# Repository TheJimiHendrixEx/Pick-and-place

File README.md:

# Pick-and-place
This repository will hold all of the code required for the user interface on a computer as well as the code that will be run on a arduino.

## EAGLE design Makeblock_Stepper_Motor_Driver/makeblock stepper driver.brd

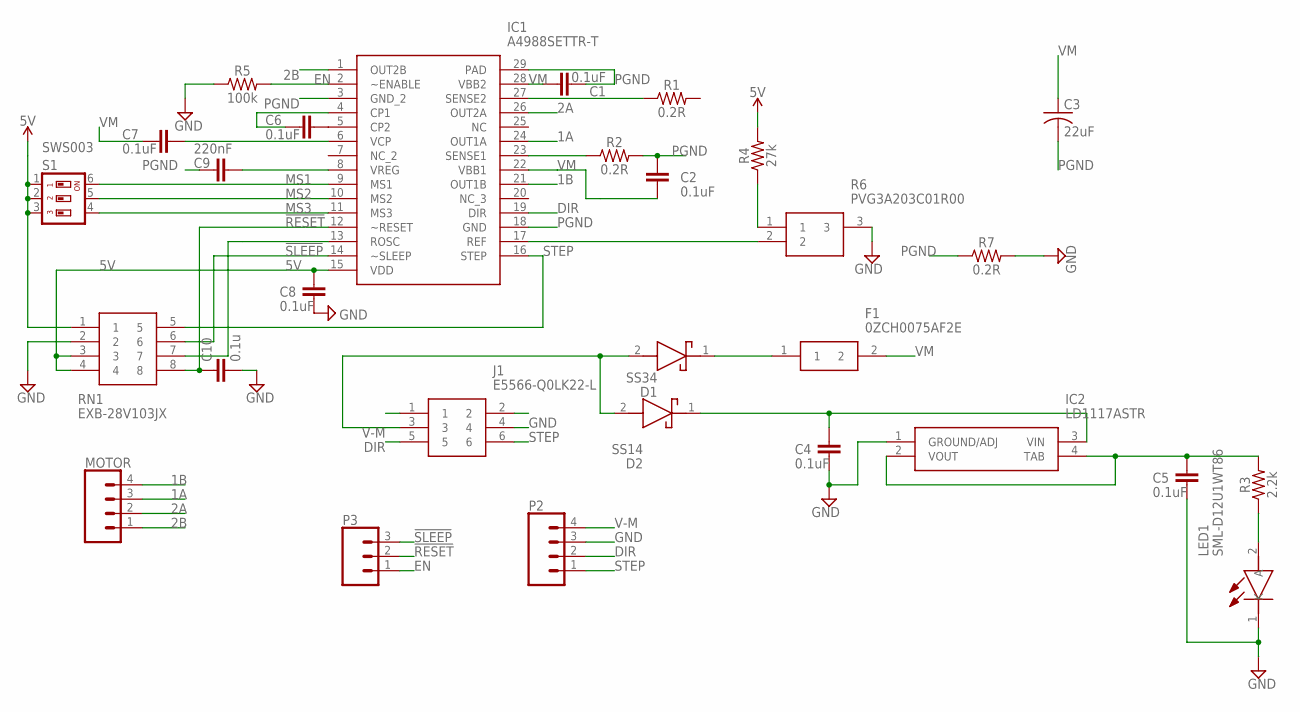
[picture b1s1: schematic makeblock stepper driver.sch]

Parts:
C1, C2, C4, C5, C6, C7, C8: 0.1uF; C0402
C3: 22uF; C025-024X044
C9: 220nF; C0402
C10: 0.1u; C0402
D1: SS34; DIOM8059X256N
D2: SS14; DIOM5227X270N
F1: 0ZCH0075AF2E; FUSC3226X75N
IC1: A4988SETTR-T; QFN50P500X500X100-29N
IC2: LD1117ASTR; SOT230P700X180-4N
J1: E5566-Q0LK22-L; E5566Q0LK22L
LED1: SML-D12U1WT86; LEDC1608X65N
MOTOR: CONN_04JST-PTH-VERT; JST-4-PTH-VERT
P2: CONN_04PTH; 1X04
P3: CONN_03LOCK; 1X03_LOCK
R1, R2, R7: 0.2R; 0603
R3: 2.2k; 0603
R4: 27k; 0603
R5: 100k; 0603
R6: PVG3A203C01R00
RN1: EXB-28V103JX; EXB28V_1
S1: SWS003; SMS-003

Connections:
1A: IC1.24 (OUT1A), MOTOR.3
1B: IC1.21 (OUT1B), MOTOR.4
2A: IC1.26 (OUT2A), MOTOR.2
2B: IC1.1 (OUT2B), MOTOR.1
5V: C8.2, IC1.15 (VDD), R4.2, RN1.1, RN1.3, RN1.4, S1.1, S1.2, S1.3
!RESET: C10.1, IC1.12 (~RESET), P3.2, RN1.8
!SLEEP: IC1.14 (~SLEEP), P3.3, RN1.6
DIR: IC1.19 (DIR), J1.5, P2.2
EN: IC1.2 (~ENABLE), P3.1, R5.2
GND: C4.1, C5.1, C8.1, C10.2, IC2.1 (GROUND/ADJ), J1.4, LED1.1 (K), P2.3, R5.1, R6.3, R7.2, RN1.2
MS1: IC1.9 (MS1), S1.6
MS2: IC1.10 (MS2), S1.5
MS3: IC1.11 (MS3), S1.4
unnamed: C6.2, IC1.5 (CP2)
unnamed: C6.1, IC1.4 (CP1)
unnamed: D1.1 (K), F1.1
unnamed: C4.2, D2.1 (K), IC2.3 (VIN)
unnamed: C9.2, IC1.8 (VREG)
unnamed: IC1.13 (ROSC), RN1.7
unnamed: LED1.2 (A), R3.1
unnamed: C5.2, IC2.2 (VOUT), IC2.4 (TAB), R3.2
unnamed: C7.2, IC1.6 (VCP)
unnamed: IC1.27 (SENSE2), R1.1
unnamed: IC1.23 (SENSE1), R2.1
unnamed: R4.1, R6.1
unnamed: IC1.17 (REF), R6.2
PGND: C1.1, C2.1, C3.2, C9.1, IC1.3 (GND_2), IC1.18 (GND), IC1.29 (PAD), R2.2, R7.1
STEP: IC1.16 (STEP), J1.6, P2.1, RN1.5
V-M: D1.2 (A), D2.2 (A), J1.3, P2.4
VM: C1.2, C2.2, C3.1, C7.1, F1.2, IC1.22 (VBB1), IC1.28 (VBB2)

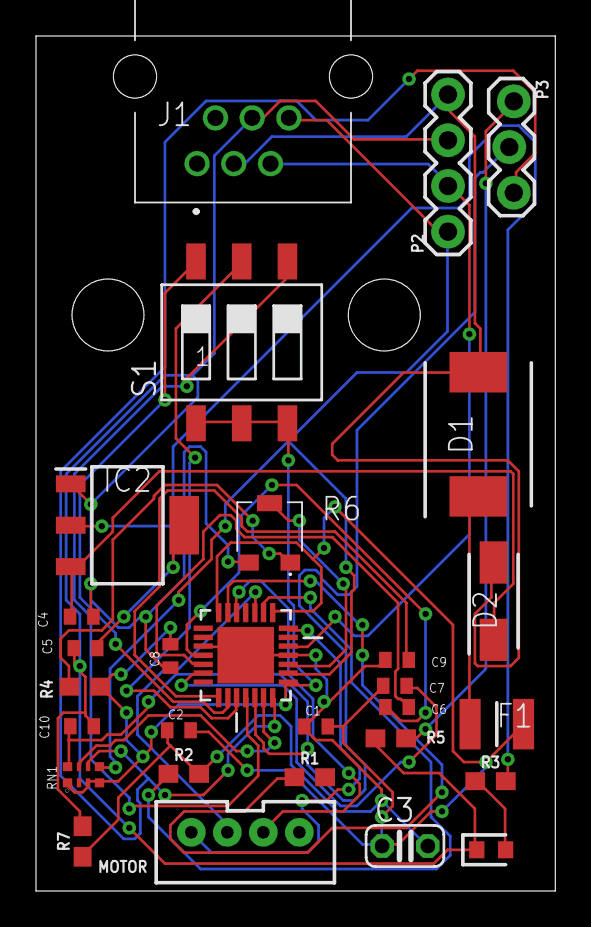
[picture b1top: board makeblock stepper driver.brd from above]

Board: 2 copper layers, 28.9 x 47.5 mm, 29 parts (0 on the bottom side), 30 nets.

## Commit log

2019-02-02 This is the first commit
2019-02-02 Deleted the temp files
2019-02-02 test commit
2019-02-02 homework
2019-02-02 deleting temp code
2019-02-05 test
2019-02-11 Created a visual studio project
2019-02-11 This is actually the project
2019-02-11 Testing visual studio
2019-02-17 Added code for the video camera
2019-02-17 All the gcode parser
2019-03-03 Installed the correct gcode parser
2019-03-08 Added keyPress event listeners, more buttons, and started to organize the controls
2019-04-06 Fixed the z axis on arduino code, added functionality to the x y and z buttons.
2019-04-07 borders and layout changes
2019-04-08 Reorganizing the UI, Resized Video Feed
2019-04-08 Added Colors
2019-04-08 dark blue border around the video feed
2019-04-09 added zero angle buton, offset functions, and offset return
2019-04-09 GUI: Added new Gcodes for zeroing
2019-04-09 added Gcode93-95
2019-04-10 added XYZA textboxes for displaying current coords
2019-04-10 added connection status box
2019-04-22 makeblock stepper motor schematic started
2019-04-22 I added a dependancy property that wull update a text box :wq
2019-04-23 Added parts to the schematic
2019-04-28 Finshed the schematic and the layout
2019-05-03 Added functionality to the zero buttons, included the lcd code in arduino,
2019-05-05 Z Stepper Limiter, A Stepper Motor functionality, New LCD custom message
2019-05-06 Added solenoid stuff
2019-05-06 button for solenoid
2019-05-06 Fixed "Go Home", Fixed Offset, Added Feedrate Control
2019-05-07 added set your own coords, feedrate notes, reorganized right pane
2019-05-07 Added Max Feedrate Notes
2019-05-08 Added text alignment for text inside textbox
2020-03-31 changed error popup

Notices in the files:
parts and their libraries:
SparkFun-Connectors: Licensing: Creative Commons ShareAlike 4.0 International - https://creativecommons.org/licenses/by-sa/4.0
